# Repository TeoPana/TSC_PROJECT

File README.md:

# TSC_PROJECT
                    DIAGRAMA

                 +----------------------+
                 |      Baterie LiPo    |
                 +----------+-----------+
                            |
                            v
                 +----------------------+
                 |   Bloc alimentare    |
                 |  Charger / DC-DC     |
                 |  VBUS / VBAT / 3V3   |
                 +----------+-----------+
                            |
                            v
                 +----------------------+
                 |      nRF52840        |
                 | MCU + BLE + control  |
                 +---+---------+-----+--+
                     |         |     |
          SPI        |         |     | GPIO
                     |         |     |
                     v         v     v
          +---------------+  +-------------+  +-------------+
          |  Display      |  |  Senzori    |  |  Butoane    |
          |  e-paper      |  |  IMU / I2C  |  |  User Input |
          +---------------+  +-------------+  +-------------+

                     |
                     | SWD / test pads
                     v
              +------------------+
              | Debug / Program  |
              | SWDIO / SWDCLK   |
              +------------------+

                     |
                     | RF matching
                     v
              +------------------+
              | Antena 2.4 GHz   |
              +------------------+

USB-C ---> Alimentare / Service / Debug

Descriere Hardware - Proiect Smartwatch
Ce am vrut să fac aici e un smartwatch care are la bază microcontrolerul nRF52840. L-am ales pe ăsta pentru că e destul de puternic, are nucleu ARM Cortex-M4F și vine deja cu partea de radio de 2.4 GHz integrată, deci ne scapă de multe bătăi de cap cu comunicarea. El se ocupă de tot: display, butoane, baterie și partea de bluetooth.

1. Cum e gândit sistemul
Toată treaba e alimentată de o baterie mică Li-Po. Am pus niște test pad-uri pe placă ca să o putem lipi ușor. Tensiunea trece printr-un etaj de conversie (un DC/DC) și apoi pleacă spre restul componentelor.

În mare, piesa centrală (nRF-ul) coordonează:

Ecranul de tip e-paper (care consumă super puțin);

Senzorii de pe magistrala serială;

Butoanele pentru utilizator;

Partea de programare (debug) și antena de radio.

Cam astea ar fi blocurile mari: alimentare, procesorul, afișajul, butoanele și partea de RF.

2. Alimentarea
Bateria Li-Po e legată direct la PCB. Ca să scoatem 3.3 V pentru microcontroler am folosit un convertor DC/DC step-up (mă rog, e de tip step-down pentru că bateria are cam 3.7V-4.2V, dar ideea e că stabilizează rail-ul principal).

Am pus și condensatori de filtrare, de 100 nF, pe care i-am înghesuit cât mai aproape de pinii de alimentare, ca să nu avem zgomot. Traseele de curent le-am făcut mai groase pe cablaj ca să nu se încălzească sau să avem căderi de tensiune. Am mers pe DC/DC în loc de regulator liniar (LDO) ca să țină bateria mai mult, că la un ceas e critică autonomia.

3. Creierul sistemului (nRF52840)
Ăsta e punctul central. nRF-ul face de toate: citește butoanele, trimite date la ecran și se ocupă de stările de „sleep” ca să economisească energie. L-am pus cam pe mijlocul plăcii ca să fie traseele scurte către toate componentele și să nu se bată cap în cap semnalele digitale cu cele de radio.

4. Display-ul și cum se vede imaginea
Ecranul e legat prin SPI. Am ales SPI pentru că e mult mai rapid ca I2C-ul și la un ecran grafic chiar ai nevoie de viteză ca să nu se vadă cum se desenează pixelii.
Semnalele pe care le folosim sunt: MOSI pentru date, SCK (ceasul), CS (ca să știe display-ul că vorbim cu el) și mai sunt pinii de Reset și Busy.

Conectorul pentru display e pus pe margine, ca să poată intra panglica aia flexibilă în carcasă fără să se îndoaie prea tare sau să atingă alte piese.

5. Senzori și alte conexiuni
Pentru restul senzorilor am folosit magistrala I2C. E mai simplu așa că folosim doar doi pini (SDA și SCL) și putem pune mai mulți senzori pe aceleași fire. Am pus și rezistențe de pull-up, că altfel nu merge comunicarea pe I2C, e o greșeală clasică pe care am vrut să o evit.

6. Butoane (Input)
Am pus niște butoane fizice legate la pinii de tip GPIO. Din soft o să facem debouncing, dar pe parte de hardware sunt legate direct. Sunt puse pe margini ca să se pupe cu decupajele din carcasa printată.

7. USB-ul și programarea
Avem un conector USB-C pentru încărcare. Pentru programare n-am mai pus mufă specială că ocupa loc, așa că am scos niște pad-uri de test (SWDIO, SWDCLK, etc) unde ne putem lipi cu un programator extern când facem debug. E mult mai ok așa pentru faza de prototip.

8. Partea de antenă (RF)
Aici e cea mai sensibilă zonă. Am urmat schema de referință cu niște bobine și condensatori (rețeaua de adaptare) ca să avem impedanța de 50 ohmi.
Câteva reguli pe care le-am respectat la layout:

Antena e fix pe marginea plăcii;

Nu am pus masă (ground) sub antenă că altfel nu mai emite nimic;

Traseul e cât mai scurt, fără unghiuri dubioase care să bage paraziți.

9. Designul cablajului (Layout)
Am încercat să grupez piesele logic. Condensatorii de decuplare sunt „lipiți” de pinii de alimentare. N-am folosit unghiuri de 90 de grade la trasee (am mers pe 45) ca să arate profi și să evităm problemele de reflexie a semnalului. Am pus plan de masă pe ambele fețe și multe via-uri (via stitching) ca să fie totul ecranat bine, mai ales lângă zona de radio.

10. Bateria și consumul
Ceasul trebuie să stea aprins mult, deci am setat nRF-ul să stea în low-power cât mai mult timp. Ecranul e-paper ajută enorm aici, că el consumă curent doar când schimbi imaginea, în rest stă „degeaba”. Dacă nu facem refresh des, bateria ar trebui să țină destul de bine.

11. Cum se asamblează toate (Mecanică)
În modelul 3D am verificat dacă încap toate: PCB-ul, bateria Li-Po (care e destul de grasă) și ecranul. Mufa USB-C trebuie să iasă fix prin gaura din carcasă, altfel nu putem băga cablul la încărcat. Per total, totul pare că se aliniază ok și nu există piese care să se lovească între ele.

## Bill of Materials (BOM)

| Ref | Componentă | Valoare | Package | JLC Part | Datasheet |
|-----|------------|--------|--------|----------|-----------|
| C5, C7, C8, C12, C19 | Condensator decuplare | 100nF | 0201 | C1525 | https://datasheet.lcsc.com/lcsc/1811091111_Murata-Electronics-GRM011R60J104KE01D_C1525.pdf |
| C23, C27, C34, C42 | Condensator | 100nF | 0201 | C1525 | https://datasheet.lcsc.com/lcsc/1811091111_Murata-Electronics-GRM011R60J104KE01D_C1525.pdf |
| C15 | Condensator | 1µF | 0402 | C52923 | https://datasheet.lcsc.com/lcsc/1811151714_Samsung-Electro-Mechanics-CL05A105KO5NNNC_C52923.pdf |
| C24, C39 | Condensator bulk | 10µF | 0402 | C19702 | https://datasheet.lcsc.com/lcsc/1811091111_Samsung-Electro-Mechanics-CL05A106MQ5NUNC_C19702.pdf |
| C11 | Condensator RF | 100pF | 0201 | C57112 | https://datasheet.lcsc.com/lcsc/1811151714_Samsung-Electro-Mechanics-CL03C101JB3NNNC_C57112.pdf |
| R5, R7, R8 | Rezistor | 10kΩ | 0201 | C25744 | https://datasheet.lcsc.com/lcsc/1811090913_Yageo-RC0201FR-0710KL_C25744.pdf |
| R9, R_PWR_EPD | Rezistor | 10kΩ | 0201 | C25744 | https://datasheet.lcsc.com/lcsc/1811090913_Yageo-RC0201FR-0710KL_C25744.pdf |
| L2 | Inductor | 10µH | 0402 | C1046 | https://datasheet.lcsc.com/lcsc/1811091211_Sunlord-SWPA4020S100MT_C1046.pdf |
| SJ1 | Jumper | - | SMD | - | - |
| U1 | Microcontroller | nRF52840 | QFN/BGA | C87453 | https://infocenter.nordicsemi.com/pdf/nRF52840_PS_v1.1.pdf |
| USB | Conector USB-C | - | SMD | C165948 | https://datasheet.lcsc.com/lcsc/1811151713_TYPE-C-16PIN_C165948.pdf |
Toate componentele au fost selectate din biblioteca JLCPCB pentru a asigura compatibilitatea cu procesul de asamblare automată.

PINII nRF52840

Pinii i-am ales în funcție de cum dădea mai bine pe layout-ul PCB-ului și cum se optimiza mai ușor rutarea. Perifericele, gen SPI și I2C, le-am mapat pe pinii care erau cei mai aproape de componentele lor, special ca să ținem traseele scurte și să nu avem zgomot pe semnal.

Pinii cu funcții speciale (SWD și resetul) i-am lăsat doar pentru partea de debug, nu i-am folosit la alte semnale de uz general ca să nu ne încurcăm. Pentru semnalele de viteză mare, cum e SPI-ul, am mers pe conexiuni cât mai scurte și directe, în timp ce pe alea mai lente (I2C sau GPIO-urile) le-am plasat mai flexibil, pe unde am mai găsit loc pe placă.

Aveam si componenta 3D a TC2030-IDC ului, dar dupa ce am vorbit cu laborantul despre problema ca nu ar incapea in carcasa toate acele cabluri, mi s-a spus ca trebuie sa sterg acel model, si doar sa pun un rectangle deasupra lui ca sa acopar acele gauri.

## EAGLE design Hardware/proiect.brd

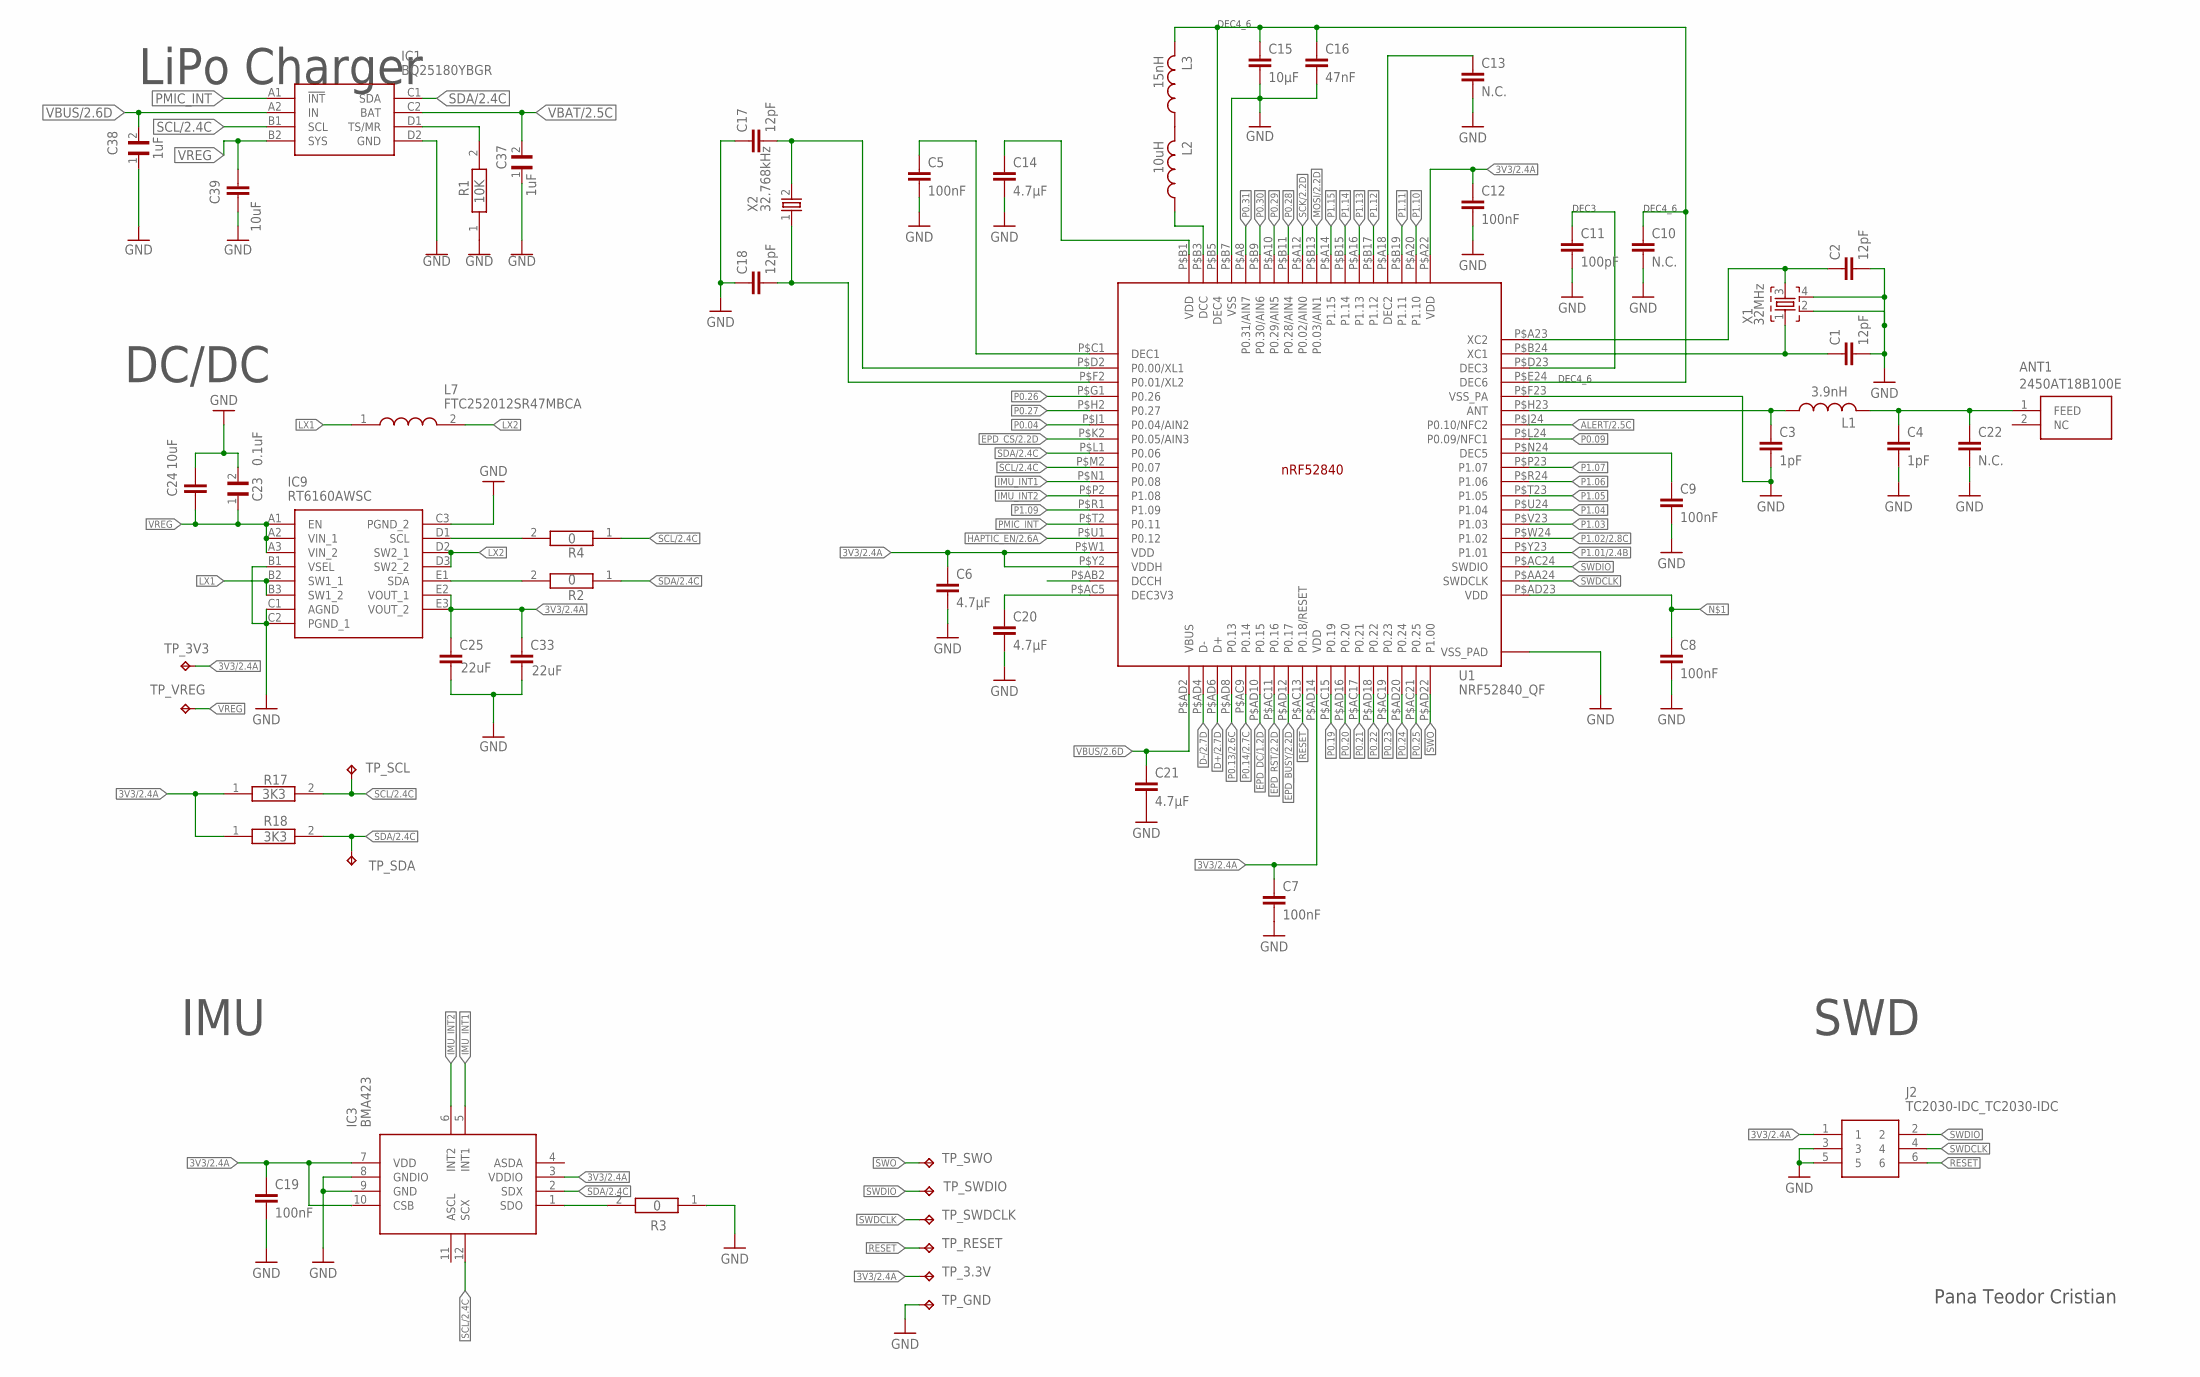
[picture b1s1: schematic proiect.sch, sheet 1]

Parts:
ANT1: 2450AT18B100E; 2450AT18B100E_ANTC3216X140N
C1, C2, C17, C18: 12pF; PERFECT_0402_0402
C3, C4: 1pF; NORDIC_NRF_3_RESC0201_L
C5, C7, C8, C9: 100nF; NORDIC_NRF_3_RESC0201_L
C6, C14, C20: 4.7µF; PERFECT_0402_0402
C10, C13: N.C.; PERFECT_0402_0402
C11: 100pF; PERFECT_0402_0402
C12, C19: 100nF; PERFECT_0402_0402
C15: 10µF; PERFECT_0402_0402
C16: 47nF; PERFECT_0402_0402
C21: 4.7µF; NORDIC_NRF_3_RESC0201_L
C22: N.C.; NORDIC_NRF_3_RESC0201_L
C23: 0.1uF; GRM011R60J152KE01L_2_CAPC0201X13N
C24: 10uF; PERFECT_0402_0402
C25, C33: 22uF; PERFECT_0402_0402
C37: 1uF; GRM011R60J152KE01L_2_CAPC0201X13N
C38: 1uF; GRM011R60J152KE01L_1_0201
C39: 10uF; NORDIC_NRF_3_RESC0201_L
IC1: BQ25180YBGR; BQ25180YBGR_BGA8C40P2X4_100X155X50
IC3: BMA423; BMA423_BMA423
IC9: RT6160AWSC; RT6160AWSC_BGA15C40P3X5_140X230X60
J2: TC2030-IDC_TC2030-IDC; TC2030-IDC_TC2030IDC
L1: 3.9nH; NORDIC_NRF_2_RESC0402_L
L2: 10uH; NORDIC_NRF_2_RESC0402_L
L3: 15nH; NORDIC_NRF_2_RESC0402_L
L7: FTC252012SR47MBCA; MLP2016SR47MT0S1_INDC2016X100N
R1: 10K; CPF0201D7K68C1_0201
R2, R3, R4: 0; CPF0201D7K68C1_0201
R17, R18: 3K3; CPF0201D7K68C1_0201
TP_3.3V, TP_3V3: HECTOR_WATCH_1_TPTP20R; HECTOR_WATCH_1_TP20R
TP_GND: HECTOR_WATCH_1_TPTP20R; HECTOR_WATCH_1_TP20R
TP_RESET: HECTOR_WATCH_1_TPTP20R; HECTOR_WATCH_1_TP20R
TP_SCL: HECTOR_WATCH_1_TPTP20R; HECTOR_WATCH_1_TP20R
TP_SDA: HECTOR_WATCH_1_TPTP20R; HECTOR_WATCH_1_TP20R
TP_SWDCLK: HECTOR_WATCH_1_TPTP20R; HECTOR_WATCH_1_TP20R
TP_SWDIO: HECTOR_WATCH_1_TPTP20R; HECTOR_WATCH_1_TP20R
TP_SWO: HECTOR_WATCH_1_TPTP20R; HECTOR_WATCH_1_TP20R
TP_VREG: HECTOR_WATCH_1_TPTP20R; HECTOR_WATCH_1_TP20R
U1: NRF52840_QF; NORDIC_NRF_4_AQFN50P700X700X85_HS-74N
X1: 32MHz; NORDIC_NRF_BT-XTAL_2016_N
X2: 32.768kHz; NORDIC_NRF_1_XTAL_3215_N

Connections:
3V3/2.4A: C6.1, C7.1, C12.1, C19.1, C25.1, C33.1, IC3.3 (VDDIO), IC3.7 (VDD), IC3.10 (CSB), IC9.E2 (VOUT_1), IC9.E3 (VOUT_2), J2.1, R17.1, R18.1, TP_3.3V.TP, TP_3V3.TP, U1.P$A22 (VDD), U1.P$AD14 (VDD), U1.P$W1 (VDD), U1.P$Y2 (VDDH)
ALERT/2.5C: U1.P$J24 (P0.10/NFC2)
D+/2.7D: U1.P$AD6 (D+)
D-/2.7D: U1.P$AD4 (D-)
EPD_BUSY/2.2D: U1.P$AD12 (P0.17)
EPD_CS/2.2D: U1.P$K2 (P0.05/AIN3)
EPD_DC/1.2D: U1.P$AD10 (P0.15)
EPD_RST/2.2D: U1.P$AC11 (P0.16)
GND: C1.2, C2.2, C3.2, C4.2, C5.2, C6.2, C7.2, C8.2, C9.2, C10.2, C11.2, C12.2, C13.2, C14.2, C15.2, C16.2, C17.1, C18.1, C19.2, C20.2, C21.2, C22.2, C23.2, C24.1, C25.2, C33.2, C37.1, C38.1, C39.2, IC1.D2 (GND), IC3.8 (GNDIO), IC3.9 (GND), IC9.B1 (VSEL), IC9.C1 (AGND), IC9.C2 (PGND_1), IC9.C3 (PGND_2), J2.3, J2.5, R1.1, R3.1, TP_GND.TP, U1.P$74 (VSS_PAD), U1.P$75 (VSS_PAD), U1.P$76 (VSS_PAD), U1.P$77 (VSS_PAD), U1.P$78 (VSS_PAD), U1.P$79 (VSS_PAD), U1.P$80 (VSS_PAD), U1.P$81 (VSS_PAD), U1.P$82 (VSS_PAD), U1.P$83 (VSS_PAD), U1.P$84 (VSS_PAD), U1.P$85 (VSS_PAD), U1.P$86 (VSS_PAD), U1.P$87 (VSS_PAD), U1.P$88 (VSS_PAD), U1.P$89 (VSS_PAD), U1.P$90 (VSS_PAD), U1.P$B7 (VSS), U1.P$F23 (VSS_PA), X1.2, X1.4; also elsewhere on the board
HAPTIC_EN/2.6A: U1.P$U1 (P0.12)
IMU_INT1: IC3.5 (INT1), U1.P$N1 (P0.08)
IMU_INT2: IC3.6 (INT2), U1.P$P2 (P1.08)
LX1: IC9.B2 (SW1_1), IC9.B3 (SW1_2), L7.1
LX2: IC9.D2 (SW2_1), IC9.D3 (SW2_2), L7.2
MOSI/2.2D: U1.P$B13 (P0.03/AIN1)
unnamed: C8.1, U1.P$AD23 (VDD)
unnamed: IC1.D1 (TS/MR), R1.2
unnamed: IC9.D1 (SCL), R4.2
unnamed: IC9.E1 (SDA), R2.2
unnamed: IC3.1 (SDO), R3.2
unnamed: C9.1, U1.P$N24 (DEC5)
unnamed: C3.1, L1.1, U1.P$H23 (ANT)
unnamed: L2.2, L3.1
unnamed: C10.1, C15.1, C16.1, L3.2, U1.P$B5 (DEC4), U1.P$E24 (DEC6)
unnamed: C11.1, U1.P$D23 (DEC3)
unnamed: C1.1, U1.P$B24 (XC1), X1.1
unnamed: C2.1, U1.P$A23 (XC2), X1.3
unnamed: ANT1.1 (FEED), C4.1, C22.1, L1.2
unnamed: C5.1, U1.P$C1 (DEC1)
unnamed: C13.1, U1.P$A18 (DEC2)
unnamed: C17.2, U1.P$D2 (P0.00/XL1), X2.2
unnamed: L2.1, U1.P$B3 (DCC)
unnamed: C14.1, U1.P$B1 (VDD)
unnamed: C18.2, U1.P$F2 (P0.01/XL2), X2.1
unnamed: C20.1, U1.P$AC5 (DEC3V3)
P0.04: U1.P$J1 (P0.04/AIN2)
P0.09: U1.P$L24 (P0.09/NFC1)
P0.13/2.6C: U1.P$AD8 (P0.13)
P0.14/2.7C: U1.P$AC9 (P0.14)
P0.19: U1.P$AC15 (P0.19)
P0.20: U1.P$AD16 (P0.20)
P0.21: U1.P$AC17 (P0.21)
P0.22: U1.P$AD18 (P0.22)
P0.23: U1.P$AC19 (P0.23)
P0.24: U1.P$AD20 (P0.24)
P0.25: U1.P$AC21 (P0.25)
P0.26: U1.P$G1 (P0.26)
P0.27: U1.P$H2 (P0.27)
P0.28: U1.P$B11 (P0.28/AIN4)
P0.29: U1.P$A10 (P0.29/AIN5)
P0.30: U1.P$B9 (P0.30/AIN6)
P0.31: U1.P$A8 (P0.31/AIN7)
P1.01/2.4B: U1.P$Y23 (P1.01)
P1.02/2.8C: U1.P$W24 (P1.02)
P1.03: U1.P$V23 (P1.03)
P1.04: U1.P$U24 (P1.04)
P1.05: U1.P$T23 (P1.05)
P1.06: U1.P$R24 (P1.06)
P1.07: U1.P$P23 (P1.07)
P1.09: U1.P$R1 (P1.09)
P1.10: U1.P$A20 (P1.10)
P1.11: U1.P$B19 (P1.11)
P1.12: U1.P$B17 (P1.12)
P1.13: U1.P$A16 (P1.13)
P1.14: U1.P$B15 (P1.14)
P1.15: U1.P$A14 (P1.15)
PMIC_INT: IC1.A1 (!INT), U1.P$T2 (P0.11)
RESET: J2.6, TP_RESET.TP, U1.P$AC13 (P0.18/RESET)
SCK/2.2D: U1.P$A12 (P0.02/AIN0)
SCL/2.4C: IC1.B1 (SCL), IC3.12 (SCX), R4.1, R17.2, TP_SCL.TP, U1.P$M2 (P0.07)
SDA/2.4C: IC1.C1 (SDA), IC3.2 (SDX), R2.1, R18.2, TP_SDA.TP, U1.P$L1 (P0.06)
SWDCLK: J2.4, TP_SWDCLK.TP, U1.P$AA24 (SWDCLK)
SWDIO: J2.2, TP_SWDIO.TP, U1.P$AC24 (SWDIO)
SWO: TP_SWO.TP, U1.P$AD22 (P1.00)
VBAT/2.5C: C37.2, IC1.C2 (BAT)
VBUS/2.6D: C21.1, C38.2, IC1.A2 (IN), U1.P$AD2 (VBUS)
VREG: C23.1, C24.2, C39.1, IC1.B2 (SYS), IC9.A1 (EN), IC9.A2 (VIN_1), IC9.A3 (VIN_2), TP_VREG.TP

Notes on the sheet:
LiPo Charger
DC/DC
DEC4_6
DEC3
IMU
SWD
Pana Teodor Cristian

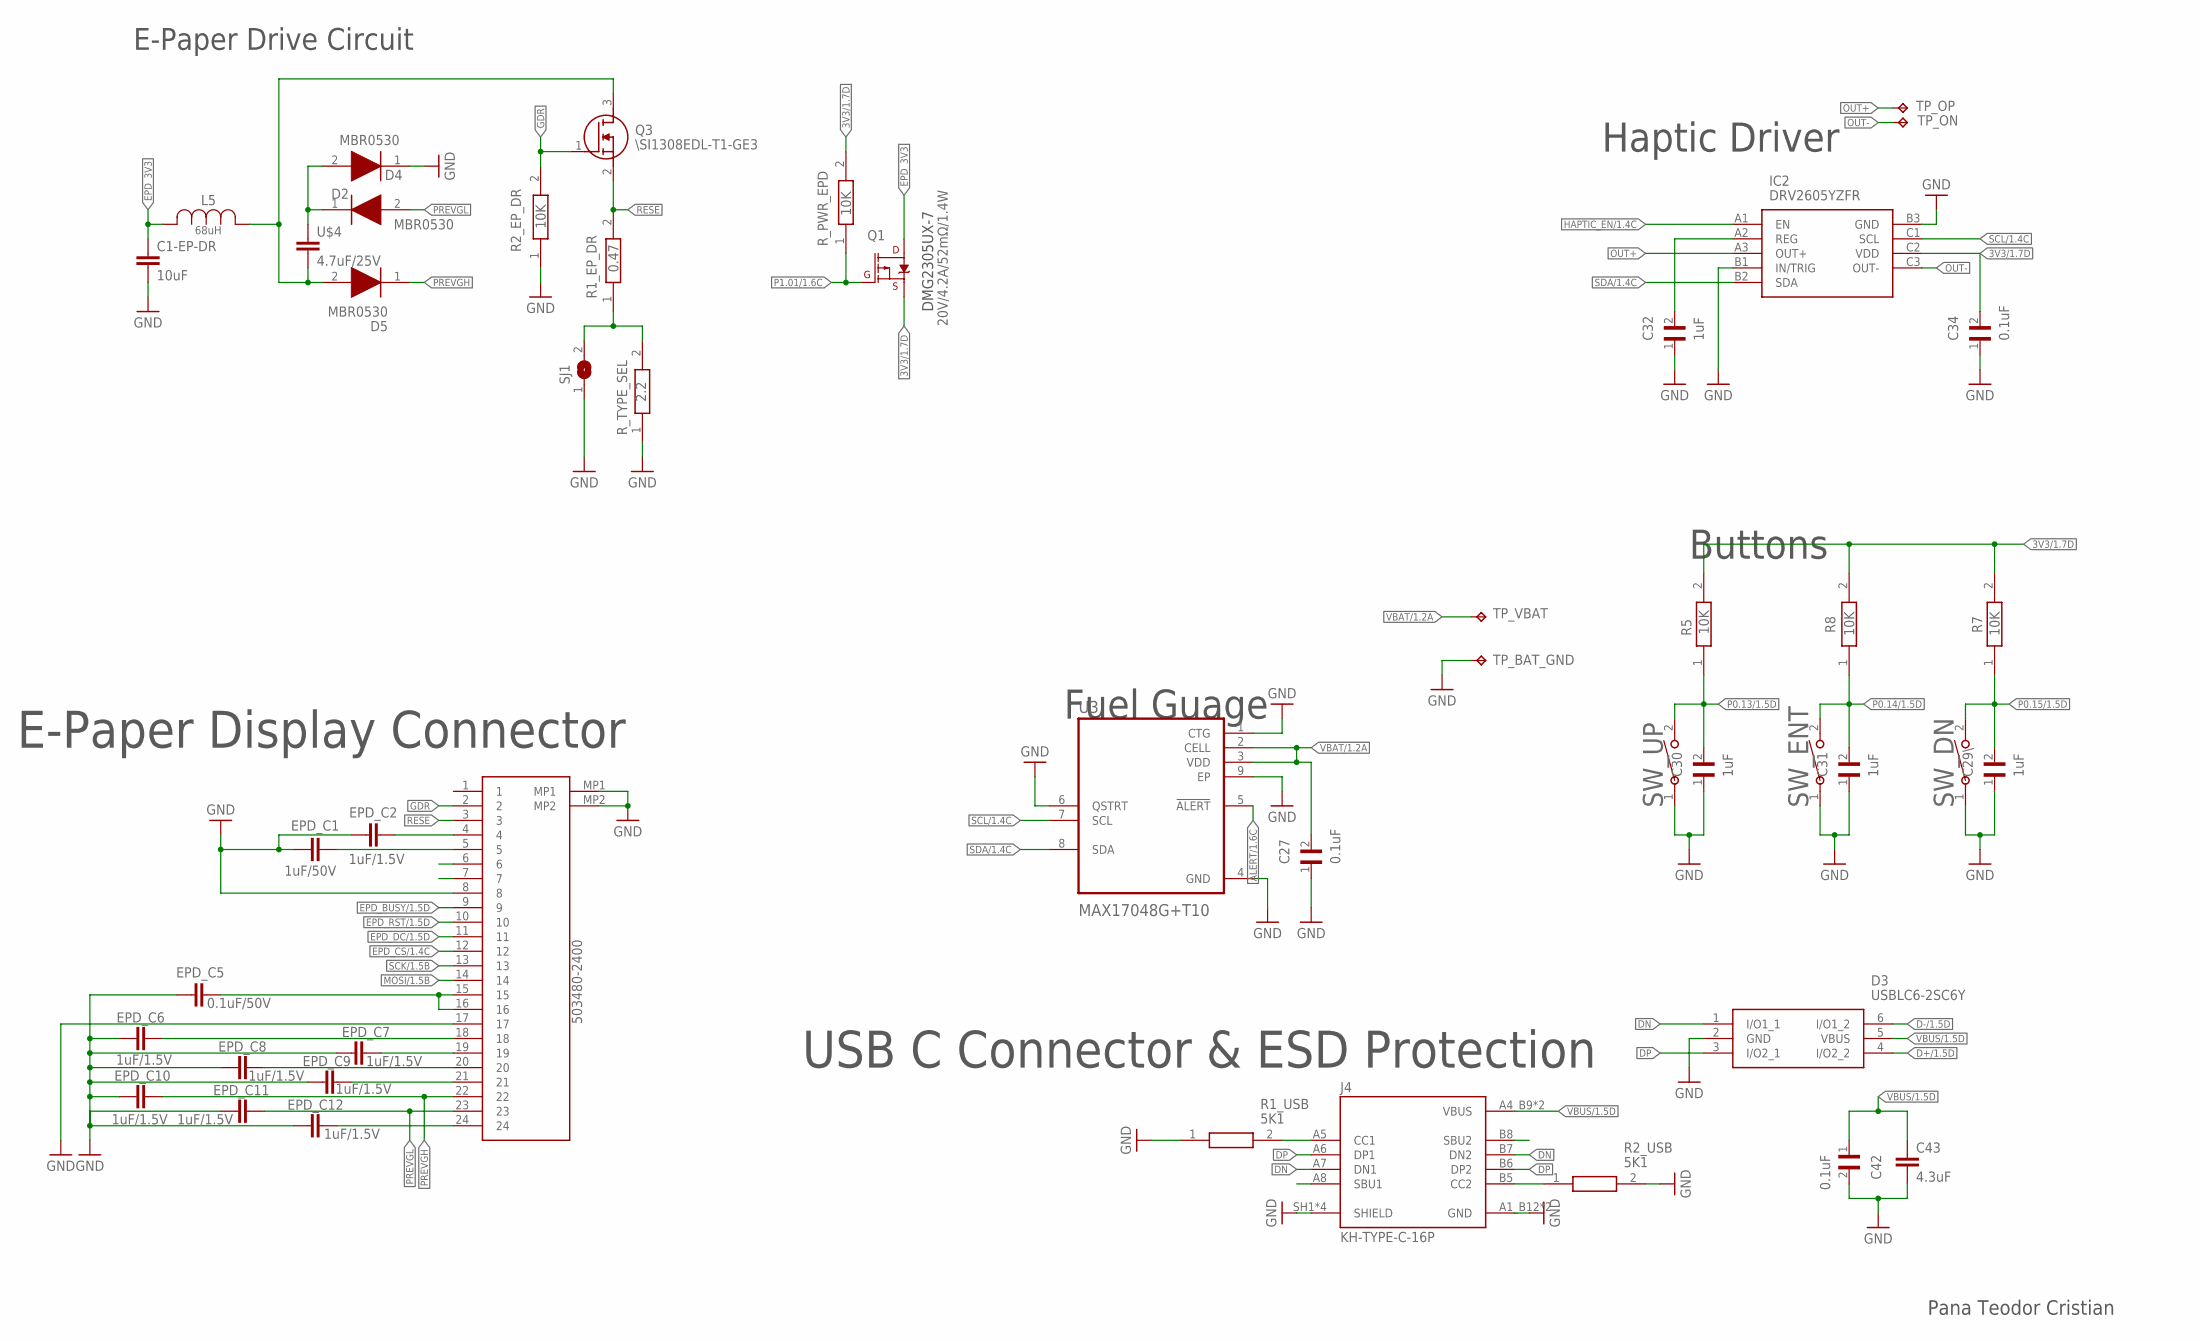
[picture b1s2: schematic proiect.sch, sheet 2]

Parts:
C1-EP-DR: 10uF; NORDIC_NRF_3_RESC0201_L
C27, C34, C42: 0.1uF; GRM011R60J152KE01L_2_CAPC0201X13N
C29\, C30, C31, C32: 1uF; GRM011R60J152KE01L_2_CAPC0201X13N
C43: 4.3uF; NORDIC_NRF_3_RESC0201_L
D2, D4, D5: MBR0530; ESP32_C6_LIBRARY_5_SOD3716X135N
D3: USBLC6-2SC6Y; ESP32_C6_LIBRARY_3_SOT95P280X145-6N
EPD_C1: 1uF/50V; PERFECT_0402_0402
EPD_C2, EPD_C6, EPD_C7, EPD_C8, EPD_C9, EPD_C10, EPD_C11, EPD_C12: 1uF/1.5V; PERFECT_0402_0402
EPD_C5: 0.1uF/50V; PERFECT_0402_0402
IC2: DRV2605YZFR; DRV2605YZFR_BGA9C50P3X3_144X144X62
J1: 503480-2400; 503480-2400_5034802400
J4: KH-TYPE-C-16P; KH-TYPE-C-16P_KINGHELM_KH-TYPE-C-16P
L5: 68uH; ESP32_C6_LIBRARY_2_IND_4828-WE-TPC_WRE
Q1: 20V/4.2A/52mΩ/1.4W; ESP32_C6_LIBRARY_4_ESP32_C6_LIBRARY_4_ESP32_C6_LIBRARY_4_ES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
Q3: \SI1308EDL-T1-GE3; ESP32_C6_LIBRARY_6_SOT65P210X110-3N
R1_EP_DR: 0.47; CPF0201D7K68C1_0201
R1_USB, R2_USB: 5K1; CPF0201D7K68C1_0201
R2_EP_DR, R5, R7, R8: 10K; CPF0201D7K68C1_0201
R_PWR_EPD: 10K; CPF0201D7K68C1_0201
R_TYPE_SEL: 2.2; CPF0201D7K68C1_0201
SJ1: ESP32_C6_LIBRARY_7_JUMPER_SJ
SW_DN: 2025-10-22_07-23-44_LIBRARY_EVP-AKE31ASW_EVP-AKE3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; 2025-10-22_07-23-44_LIBRARY_SW_EVP-AKE31A_PAN
SW_ENT: 2025-10-22_07-23-44_LIBRARY_EVP-AKE31ASW_EVP-AKE3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; 2025-10-22_07-23-44_LIBRARY_SW_EVP-AKE31A_PAN
SW_UP: 2025-10-22_07-23-44_LIBRARY_EVP-AKE31ASW_EVP-AKE3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; 2025-10-22_07-23-44_LIBRARY_SW_EVP-AKE31A_PAN
TP_BAT_GND: HECTOR_WATCH_1_TPTP20R; HECTOR_WATCH_1_TP20R
TP_ON: HECTOR_WATCH_1_TPTP20R; HECTOR_WATCH_1_TP20R
TP_OP: HECTOR_WATCH_1_TPTP20R; HECTOR_WATCH_1_TP20R
TP_VBAT: HECTOR_WATCH_1_TPTP20R; HECTOR_WATCH_1_TP20R
U3: MAX17048G+T10; ESP32_C6_LIBRARY_SON50P200X200X80-9N
U$4: 4.7uF/25V; NORDIC_NRF_3_RESC0201_L

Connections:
3V3/1.7D: C34.2, IC2.C2 (VDD), Q1.2 (S), R5.2, R7.2, R8.2, R_PWR_EPD.2
ALERT/1.6C: U3.5 (!ALERT)
D+/1.5D: D3.4 (I/O2_2)
D-/1.5D: D3.6 (I/O1_2)
DN: D3.1 (I/O1_1), J4.A7 (DN1), J4.B7 (DN2)
DP: D3.3 (I/O2_1), J4.A6 (DP1), J4.B6 (DP2)
EPD_3V3: C1-EP-DR.1, L5.2, Q1.3 (D)
EPD_BUSY/1.5D: J1.9
EPD_CS/1.4C: J1.12
EPD_DC/1.5D: J1.11
EPD_RST/1.5D: J1.10
GDR: J1.2, Q3.1 (G), R2_EP_DR.2
GND: C1-EP-DR.2, C27.1, C29\.1, C30.1, C31.1, C32.1, C34.1, C42.2, C43.2, D3.2 (GND), D4.1 (K), EPD_C1.1, EPD_C2.1, EPD_C5.1, EPD_C6.1, EPD_C7.1, EPD_C8.1, EPD_C9.1, EPD_C10.1, EPD_C11.1, EPD_C12.1, IC2.B1 (IN/TRIG), IC2.B3 (GND), J1.8, J1.17, J1.MP1, J1.MP2, J4.A1_B12 (GND), J4.A12_B1 (GND), J4.SH1 (SHIELD), J4.SH2 (SHIELD), J4.SH3 (SHIELD), J4.SH4 (SHIELD), R1_USB.1, R2_EP_DR.1, R2_USB.2, R_TYPE_SEL.1, SJ1.1, SW_DN.1, SW_ENT.1, SW_UP.1, TP_BAT_GND.TP, U3.1 (CTG), U3.4 (GND), U3.6 (QSTRT), U3.9 (EP); also elsewhere on the board
HAPTIC_EN/1.4C: IC2.A1 (EN)
MOSI/1.5B: J1.14
unnamed: D5.2 (A), L5.1, Q3.3 (D), U$4.2
unnamed: D2.1 (K), D4.2 (A), U$4.1
unnamed: EPD_C2.2, J1.4
unnamed: EPD_C1.2, J1.5
unnamed: J4.B5 (CC2), R2_USB.1
unnamed: C32.2, IC2.A2 (REG)
unnamed: EPD_C5.2, J1.15, J1.16
unnamed: J4.A5 (CC1), R1_USB.2
unnamed: EPD_C6.2, J1.18
unnamed: EPD_C7.2, J1.19
unnamed: EPD_C8.2, J1.20
unnamed: EPD_C9.2, J1.21
unnamed: R1_EP_DR.1, R_TYPE_SEL.2, SJ1.2
unnamed: EPD_C12.2, J1.24
OUT+: IC2.A3 (OUT+), TP_OP.TP
OUT-: IC2.C3 (OUT-), TP_ON.TP
P0.13/1.5D: C30.2, R5.1, SW_UP.2
P0.14/1.5D: C31.2, R8.1, SW_ENT.2
P0.15/1.5D: C29\.2, R7.1, SW_DN.2
P1.01/1.6C: Q1.1 (G), R_PWR_EPD.1
PREVGH: D5.1 (K), EPD_C10.2, J1.22
PREVGL: D2.2 (A), EPD_C11.2, J1.23
RESE: J1.3, Q3.2 (S), R1_EP_DR.2
SCK/1.5B: J1.13
SCL/1.4C: IC2.C1 (SCL), U3.7 (SCL)
SDA/1.4C: IC2.B2 (SDA), U3.8 (SDA)
VBAT/1.2A: C27.2, TP_VBAT.TP, U3.2 (CELL), U3.3 (VDD)
VBUS/1.5D: C42.1, C43.1, D3.5 (VBUS), J4.A4_B9 (VBUS), J4.A9_B4 (VBUS)

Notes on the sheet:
E-Paper Display Connector
USB C Connector & ESD Protection
Fuel Guage
Buttons
Haptic Driver
E-Paper Drive Circuit
DMG2305UX-7
Pana Teodor Cristian

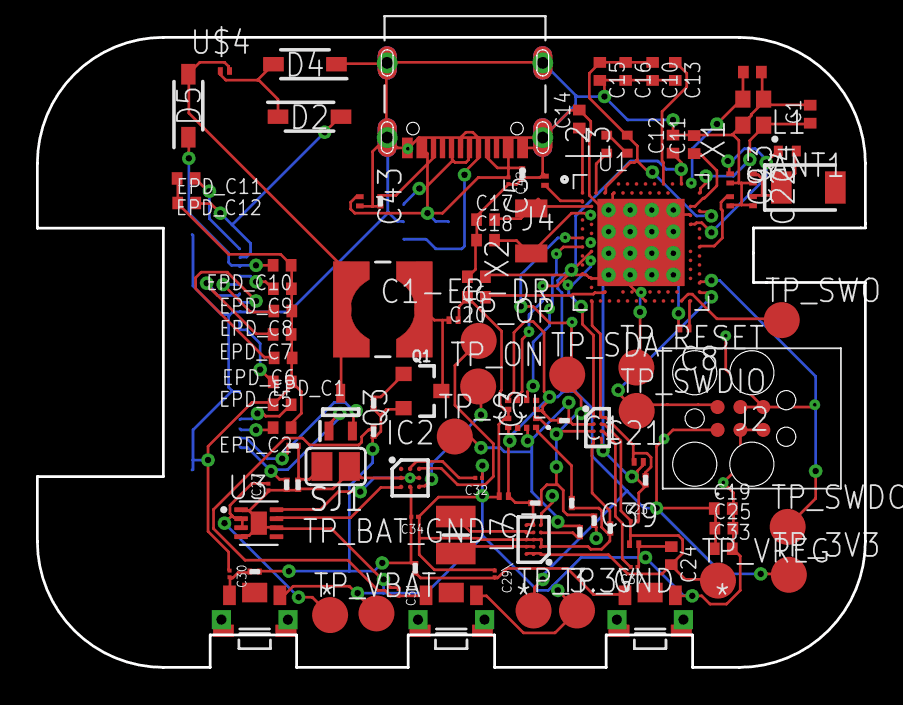
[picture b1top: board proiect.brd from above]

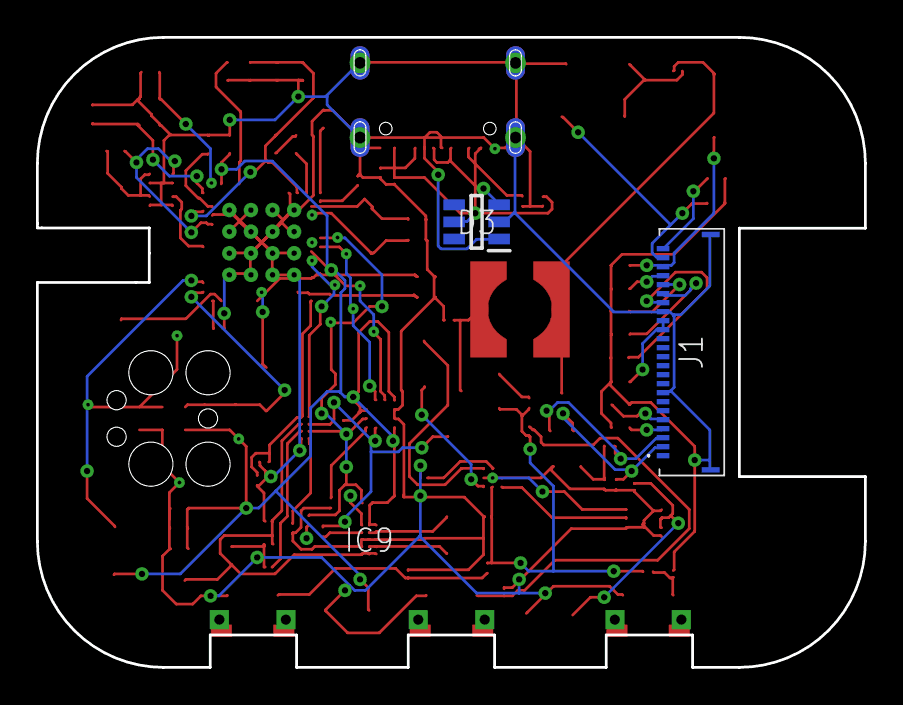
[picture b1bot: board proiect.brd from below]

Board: 4 copper layers, 46.0 x 35.0 mm, 105 parts (2 on the bottom side), 68 nets.

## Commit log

2026-04-10 todo
2026-04-10 Add files via upload
    schematic
2026-04-10 da y
2026-04-20 schematica gata
2026-04-20 update sch
2026-04-20 update brd
2026-04-21 GATA
2026-04-21 POZE
2026-04-21 README
2026-04-21 Add SCUZE.txt with display model request
    DADADADAADADADD

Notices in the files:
parts and their libraries:
COPYRIGHT: Copyright (C) 2024 Ultra Librarian. All rights reserved.
COPYRIGHT: Copyright (C) 2025 Ultra Librarian. All rights reserved.
